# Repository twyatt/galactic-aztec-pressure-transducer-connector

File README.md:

# About

Custom board used to convert 3 wire pressure transducer to ethernet plug for the [Galactic Aztec] rocket. The board was designed to interface with the [Galactic Aztec Raspberry Pi Add-on: Pressure Transducer Interface] board.

Custom EagleCAD parts on this board can be found in the [SDSU Rocket Eagle Libraries].

## Wiring
The ethernet port adheres to the following [T-568B] wiring configuration:

| Pin | Color        | Function       |
|:---:|:------------:|:--------------:|
| 1   | Orange/White | Signal         |
| 2   | Orange       | Signal         |
| 3   | Green/White  |                |
| 4   | Blue         | Supply Voltage |
| 5   | Blue/White   | Supply Voltage |
| 6   | Green        |                |
| 7   | Brown/White  | Ground         |
| 8   | Brown        | Ground         |

# Bill of Materials
| Qty | Description                               | Part Number       | Vendor   |
|:---:|-------------------------------------------|------------------:|----------|
| 1   | Jack RJ45 CAT5/CAT5e                      | [380-1046-ND]     | DigiKey  |

[Galactic Aztec]: http://rocket.sdsu.edu/rockets
[Galactic Aztec Raspberry Pi Add-on: Pressure Transducer Interface]: https://github.com/twyatt/galactic-aztec-rpi-addon-pressure
[SDSU Rocket Eagle Libraries]: https://github.com/twyatt/SDSURocket-Eagle-Libraries
[T-568B]: https://en.wikipedia.org/wiki/TIA/EIA-568#Wiring
[380-1046-ND]: http://www.digikey.com/product-detail/en/SS-7188-NF/380-1046-ND/388308

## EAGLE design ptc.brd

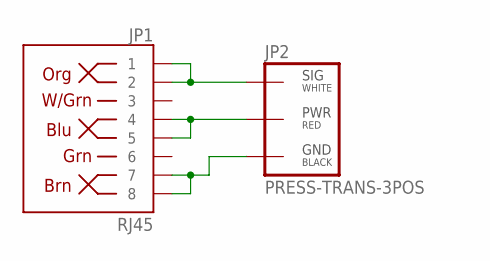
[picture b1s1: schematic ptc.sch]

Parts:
JP1: RJ45; RJ45-8
JP2: PRESS-TRANS-3POS; PRESSURE-TRANSDUCER-3POS

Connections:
unnamed: JP1.1, JP1.2, JP2.1
unnamed: JP1.4, JP1.5, JP2.2
unnamed: JP1.7, JP1.8, JP2.3

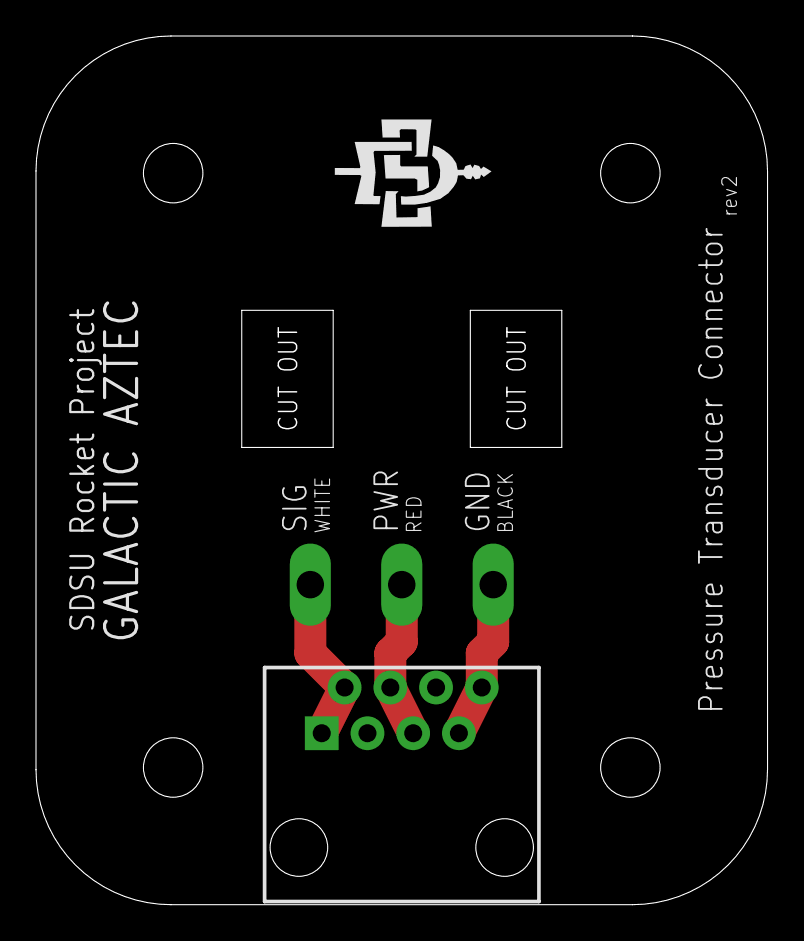
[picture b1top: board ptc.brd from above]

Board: 2 copper layers, 40.6 x 48.3 mm, 6 parts (0 on the bottom side), 3 nets.

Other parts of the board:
U$1, U$2, U$3, U$4: STAND-OFF

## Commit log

2015-07-24 Initial commit.
2015-07-24 Replaced thru holes with custom Eagle component that had larger thru holes. Adjusted cut out section. Added PCB images rendered by OSHPark. Added README.md.

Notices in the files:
parts and their libraries:
SparkFun-Connectors: Licensing: Creative Commons ShareAlike 4.0 International - https://creativecommons.org/licenses/by-sa/4.0
